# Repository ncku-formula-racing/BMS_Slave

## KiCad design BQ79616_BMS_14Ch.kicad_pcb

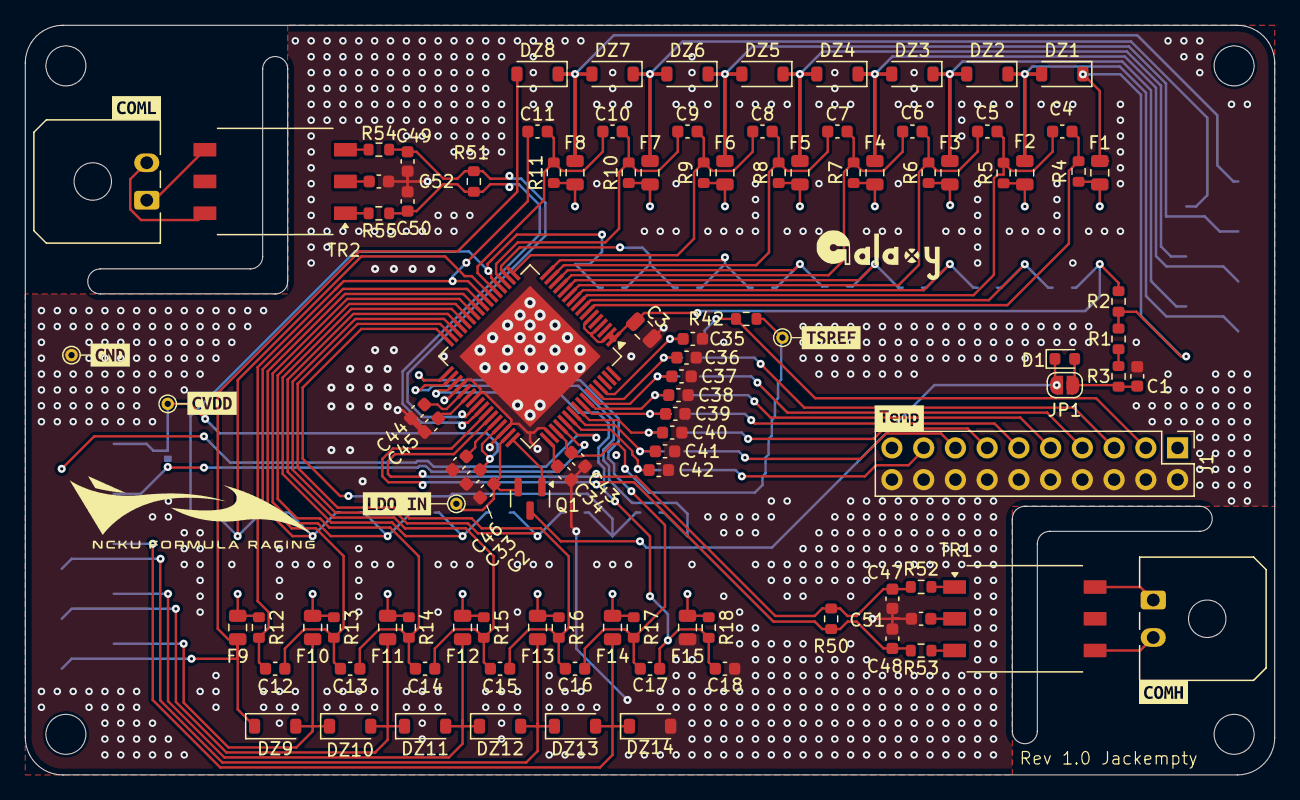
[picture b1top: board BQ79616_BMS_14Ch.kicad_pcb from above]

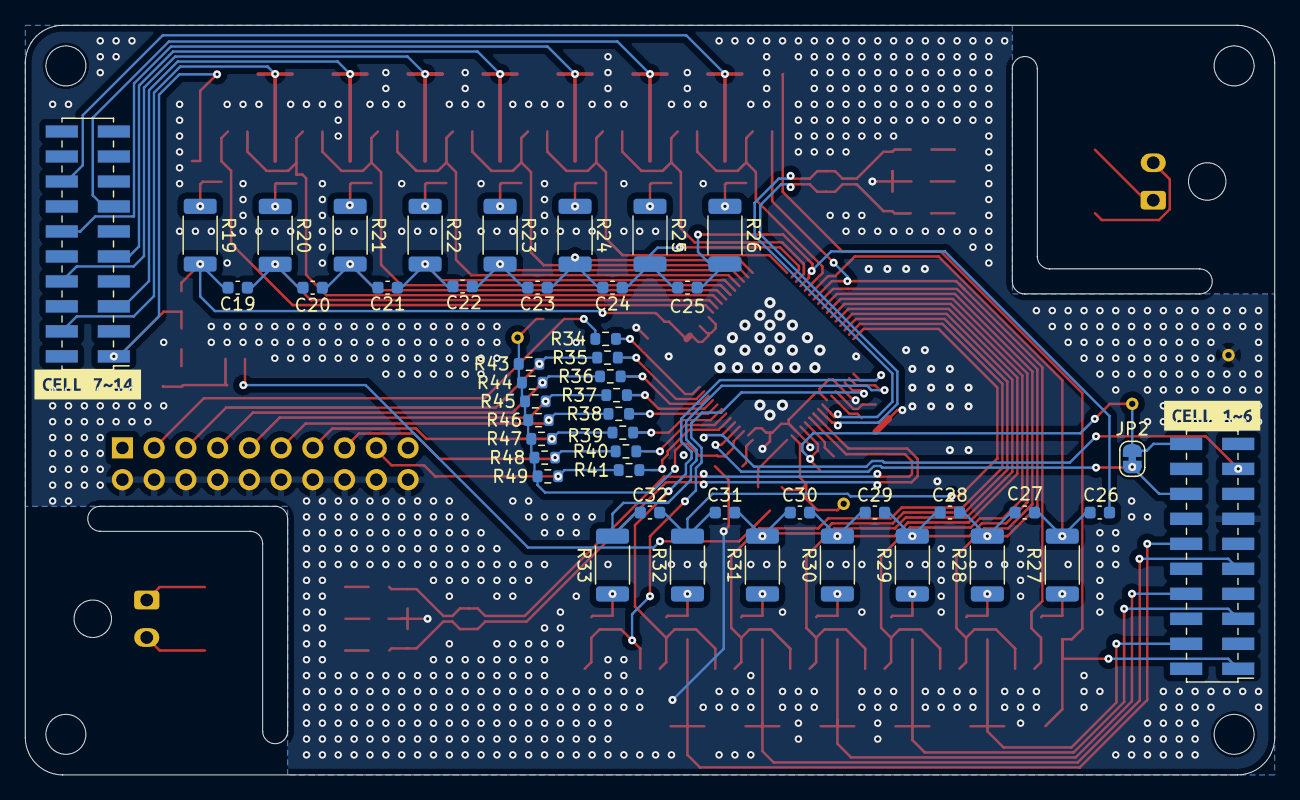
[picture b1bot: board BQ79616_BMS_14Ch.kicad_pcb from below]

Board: 2 copper layers, 100.0 x 60.0 mm, 165 parts (49 on the bottom side), 103 nets.

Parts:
C1: 220n/100V; C_0603_1608Metric
C2, C35, C36, C37, C38, C39, C40, C41, C42, C46: 100n; C_0603_1608Metric
C3: 10u; C_0805_2012Metric
C4, C5, C6, C7, C8, C9, C10, C11, C12, C13, C14, C15, C16, C17, C18, C19, C20, C21, C22, C23, C24, C25, C26, C27, C28, C29, C30, C31, C32: 470n; C_0603_1608Metric
C33: 4.7u; C_0603_1608Metric
C34: 2.2u; C_0603_1608Metric
C43, C44, C45: 1u; C_0603_1608Metric
C47, C48, C49, C50: 220p; C_0603_1608Metric
C51, C52: 100p; C_0603_1608Metric
D1: LED_PWR; LED_0603_1608Metric
DZ1, DZ2, DZ3, DZ4, DZ5, DZ6, DZ7, DZ8, DZ9, DZ10, DZ11, DZ12, DZ13, DZ14: MMSZ5232; D_SOD-123
F1, F2, F3, F4, F5, F6, F7, F8, F9, F10, F11, F12, F13, F14, F15: 0.5A Fuse; Fuse_0805_2012Metric
H1, H2, H3, H4: M3; MountingHole_3.2mm_M3_ISO7380
J1: Conn_Therm; PinHeader_2x10_P2.54mm_Vertical
J2, J3: Conn_02x10_Odd_Even; PinHeader_2x10_P2.00mm_Vertical_SMD
J4: BMS_A_OUT; Molex_Micro-Fit_3.0_43650-0200_1x02_P3.00mm_Horizontal
J5: BMS_A_IN; Molex_Micro-Fit_3.0_43650-0200_1x02_P3.00mm_Horizontal
JP1: SJ_BYPASS; SolderJumper-2_P1.3mm_Open_RoundedPad1.0x1.5mm
JP2: SolderJumper_2_Bridged; SolderJumper-2_P1.3mm_Bridged_RoundedPad1.0x1.5mm
Q1: MMBT5551; SOT-23
R1: 200R; R_0603_1608Metric
R2: 30R; R_0603_1608Metric
R3, R4, R5, R6, R7, R8, R9, R10, R11, R12, R13, R14, R15, R16, R17, R18: 100R; R_0603_1608Metric
R19, R20, R21, R22, R23, R24, R25, R26, R27, R28, R29, R30, R31, R32, R33: 10R/0.5W; R_2010_5025Metric
R34, R35, R36, R37, R38, R39, R40, R41, R50, R51: 1k; R_0603_1608Metric
R42, R43, R44, R45, R46, R47, R48, R49: 10k; R_0603_1608Metric
R52, R53, R54, R55: 49R; R_0603_1608Metric
TP1: TestPoint; TestPoint_THTPad_D1.0mm_Drill0.5mm
TP2: TP_CVDD; TestPoint_THTPad_D1.0mm_Drill0.5mm
TP3: TP_GND; TestPoint_THTPad_D1.0mm_Drill0.5mm
TP4: TP_TSREF; TestPoint_THTPad_D1.0mm_Drill0.5mm
TR1, TR2: Wuerth_750319696; Transformer_Wuerth_750315371
U1: HTQFP-64-1EP_10x10mm_P0.5mm_EP8x8mm
kibuzzard-67A37E08: G***; kibuzzard-67A37E08
kibuzzard-67A37E45: G***; kibuzzard-67A37E45
kibuzzard-67A386B0: G***; kibuzzard-67A386B0
kibuzzard-67A386E1: G***; kibuzzard-67A386E1
kibuzzard-67A3854A: G***; kibuzzard-67A3854A
kibuzzard-67A3869A: G***; kibuzzard-67A3869A
kibuzzard-67A38616: G***; kibuzzard-67A38616
kibuzzard-67A38633: G***; kibuzzard-67A38633
kibuzzard-67A38657: G***; kibuzzard-67A38657

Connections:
/AVDD_A: C45.1, U1.38 (AVDD)
/BAT_A: C3.2, C19.1, R2.2, R19.2, U1.1 (BAT), U1.2 (CB16), U1.4 (CB15), U1.6 (CB14)
/CB_A0: C32.2, R33.2, U1.34 (CB0)
/CB_A1: C31.2, C32.1, R32.2, U1.32 (CB1)
/CB_A2: C30.2, C31.1, R31.2, U1.30 (CB2)
/CB_A3: C29.2, C30.1, R30.2, U1.28 (CB3)
/CB_A4: C28.2, C29.1, R29.2, U1.26 (CB4)
/CB_A5: C27.2, C28.1, R28.2, U1.24 (CB5)
/CB_A6: C26.2, C27.1, R27.2, U1.22 (CB6)
/CB_A7: C25.2, C26.1, R26.2, U1.20 (CB7)
/CB_A8: C24.2, C25.1, R25.2, U1.18 (CB8)
/CB_A9: C23.2, C24.1, R24.2, U1.16 (CB9)
/CB_A10: C22.2, C23.1, R23.2, U1.14 (CB10)
/CB_A11: C21.2, C22.1, R22.2, U1.12 (CB11)
/CB_A12: C20.2, C21.1, R21.2, U1.10 (CB12)
/CB_A13: C19.2, C20.1, R20.2, U1.8 (CB13)
/CELL_A1: DZ13.2 (A), DZ14.1 (K), F14.1, J3.12
/CELL_A2: DZ12.2 (A), DZ13.1 (K), F13.1, J3.9
/CELL_A3: DZ11.2 (A), DZ12.1 (K), F12.1, J3.8
/CELL_A4: DZ10.2 (A), DZ11.1 (K), F11.1, J3.5
/CELL_A5: DZ9.2 (A), DZ10.1 (K), F10.1, J3.4
/CELL_A6: DZ8.2 (A), DZ9.1 (K), F9.1, J3.1
/CELL_A7: DZ7.2 (A), DZ8.1 (K), F8.1, J2.16
/CELL_A8: DZ6.2 (A), DZ7.1 (K), F7.1, J2.13
/CELL_A9: DZ5.2 (A), DZ6.1 (K), F6.1, J2.12
/CELL_A10: DZ4.2 (A), DZ5.1 (K), F5.1, J2.9
/CELL_A11: DZ3.2 (A), DZ4.1 (K), F4.1, J2.8
/CELL_A12: DZ2.2 (A), DZ3.1 (K), F3.1, J2.5
/CELL_A13: DZ1.2 (A), DZ2.1 (K), F2.1, J2.4
/CELL_A14: DZ1.1 (K), F1.1, J2.1, R1.1, R2.1
/COMHN: C48.1, R50.2, R53.1, U1.42 (COMHN)
/COMHP: C47.1, R50.1, R52.1, U1.43 (COMHP)
/COMLN: C50.1, R51.2, R55.1, U1.41 (COMLN)
/COMLP: C49.1, R51.1, R54.1, U1.40 (COMLP)
/CVDD_A: C33.1, J3.20, JP2.1 (A), TP2.1, U1.45 (CVDD)
/DVDD_A: C34.1, U1.49 (DVDD)
/GPIO_A1: C35.1, R34.1, U1.61 (GPIO1)
/GPIO_A2: C36.1, R35.1, U1.60 (GPIO2)
/GPIO_A3: C37.1, R36.1, U1.59 (GPIO3)
/GPIO_A4: C38.1, R37.1, U1.58 (GPIO4)
/GPIO_A5: C39.1, R38.1, U1.57 (GPIO5)
/GPIO_A6: C40.1, R39.1, U1.56 (GPIO6)
/GPIO_A7: C41.1, R40.1, U1.55 (GPIO7)
/GPIO_A8: C42.1, R41.1, U1.54 (GPIO8)
/LDOIN_A: C2.2, Q1.2 (E), TP1.1, U1.47 (LDOIN)
/NEG5V_A: C46.1, U1.44 (NEG5V)
/NPNB_A: Q1.1 (B), U1.48 (NPNB)
/REFHP_A: C44.1, U1.37 (REFHP)
/RX_A: J3.16, JP2.2 (B), U1.52 (RX)
/TH_A1: J1.3, R34.2, R42.2
/TH_A2: J1.5, R35.2, R43.2
/TH_A3: J1.7, R36.2, R44.2
/TH_A4: J1.9, R37.2, R45.2
/TH_A5: J1.11, R38.2, R46.2
/TH_A6: J1.13, R39.2, R47.2
/TH_A7: J1.15, R40.2, R48.2
/TH_A8: J1.17, R41.2, R49.2
/TSREF_A: C43.1, R42.1, R43.1, R44.1, R45.1, R46.1, R47.1, R48.1, R49.1, TP4.1, U1.51 (TSREF)
/TX_A: J3.17, U1.53 (TX)
/VC_A0: C17.2, C18.1, R18.2, U1.35 (VC0)
/VC_A1: C16.2, C17.1, R17.2, U1.33 (VC1)
/VC_A2: C15.2, C16.1, R16.2, U1.31 (VC2)
/VC_A3: C14.2, C15.1, R15.2, U1.29 (VC3)
/VC_A4: C13.2, C14.1, R14.2, U1.27 (VC4)
/VC_A5: C12.2, C13.1, R13.2, U1.25 (VC5)
/VC_A6: C11.2, C12.1, R12.2, U1.23 (VC6)
/VC_A7: C10.2, C11.1, R11.2, U1.21 (VC7)
/VC_A8: C9.2, C10.1, R10.2, U1.19 (VC8)
/VC_A9: C8.2, C9.1, R9.2, U1.17 (VC9)
/VC_A10: C7.2, C8.1, R8.2, U1.15 (VC10)
/VC_A11: C6.2, C7.1, R7.2, U1.13 (VC11)
/VC_A12: C5.2, C6.1, R6.2, U1.11 (VC12)
/VC_A13: C4.2, C5.1, R5.2, U1.9 (VC13)
/VC_A14: C4.1, R4.2, U1.7 (VC14)
GND1: C1.1, C2.1, C3.1, C18.2, C33.2, C34.2, C35.2, C36.2, C37.2, C38.2, C39.2, C40.2, C41.2, C42.2, C43.2, C44.2, C45.2, C46.2, C47.2, C48.2, C49.2, C50.2, C51.2, C52.2, DZ14.2 (A), F15.1, J1.2, J1.4, J1.6, J1.8, J1.10, J1.12, J1.14, J1.16, J1.18, J1.20, J3.13, TP3.1, U1.36 (REFHM), U1.39 (AVSS), U1.46 (CVSS), U1.50 (GND), U1.65
unnamed: C51.1, TR1.2
unnamed: C52.1, TR2.2
unnamed: C1.2, D1.2 (A), JP1.1 (A), R3.2
unnamed: D1.1 (K), JP1.2 (B), Q1.3 (C)
unnamed: F1.2, R4.1, R19.1
unnamed: F2.2, R5.1, R20.1
unnamed: F3.2, R6.1, R21.1
unnamed: F4.2, R7.1, R22.1
unnamed: F5.2, R8.1, R23.1
unnamed: F6.2, R9.1, R24.1
unnamed: F7.2, R10.1, R25.1
unnamed: F8.2, R11.1, R26.1
unnamed: F9.2, R12.1, R27.1
unnamed: F10.2, R13.1, R28.1
unnamed: F11.2, R14.1, R29.1
unnamed: F12.2, R15.1, R30.1
unnamed: F13.2, R16.1, R31.1
unnamed: F14.2, R17.1, R32.1
unnamed: F15.2, R18.1, R33.1
unnamed: J4.1, TR1.6
unnamed: J4.2, TR1.4
unnamed: J5.1, TR2.4
unnamed: J5.2, TR2.6
unnamed: R1.2, R3.1
unnamed: R52.2, TR1.1
unnamed: R53.2, TR1.3
unnamed: R54.2, TR2.3
unnamed: R55.2, TR2.1

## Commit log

2025-02-03 BMS slave first commit
2025-02-03 Fill all 3D model including connector and transformer
2025-02-03 Add 3D model for connector and transformer
2025-02-04 Finish positioning of all components Ver1ST
2025-02-05 Save for further try on re-configure of pin position
2025-02-05 Add gitignore
2025-02-05 Remove untracked files
2025-02-05 Finish layout for basic need, waited to add logos and labels
2025-02-05 Fix crystal pinout connection
2025-02-24 BMS v0.0.2
    Use external FET for balancing
